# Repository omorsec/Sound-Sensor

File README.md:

# Sound-Sensor
It is a device that can be used to take input from the microphone and analyze it through different microcontrollers

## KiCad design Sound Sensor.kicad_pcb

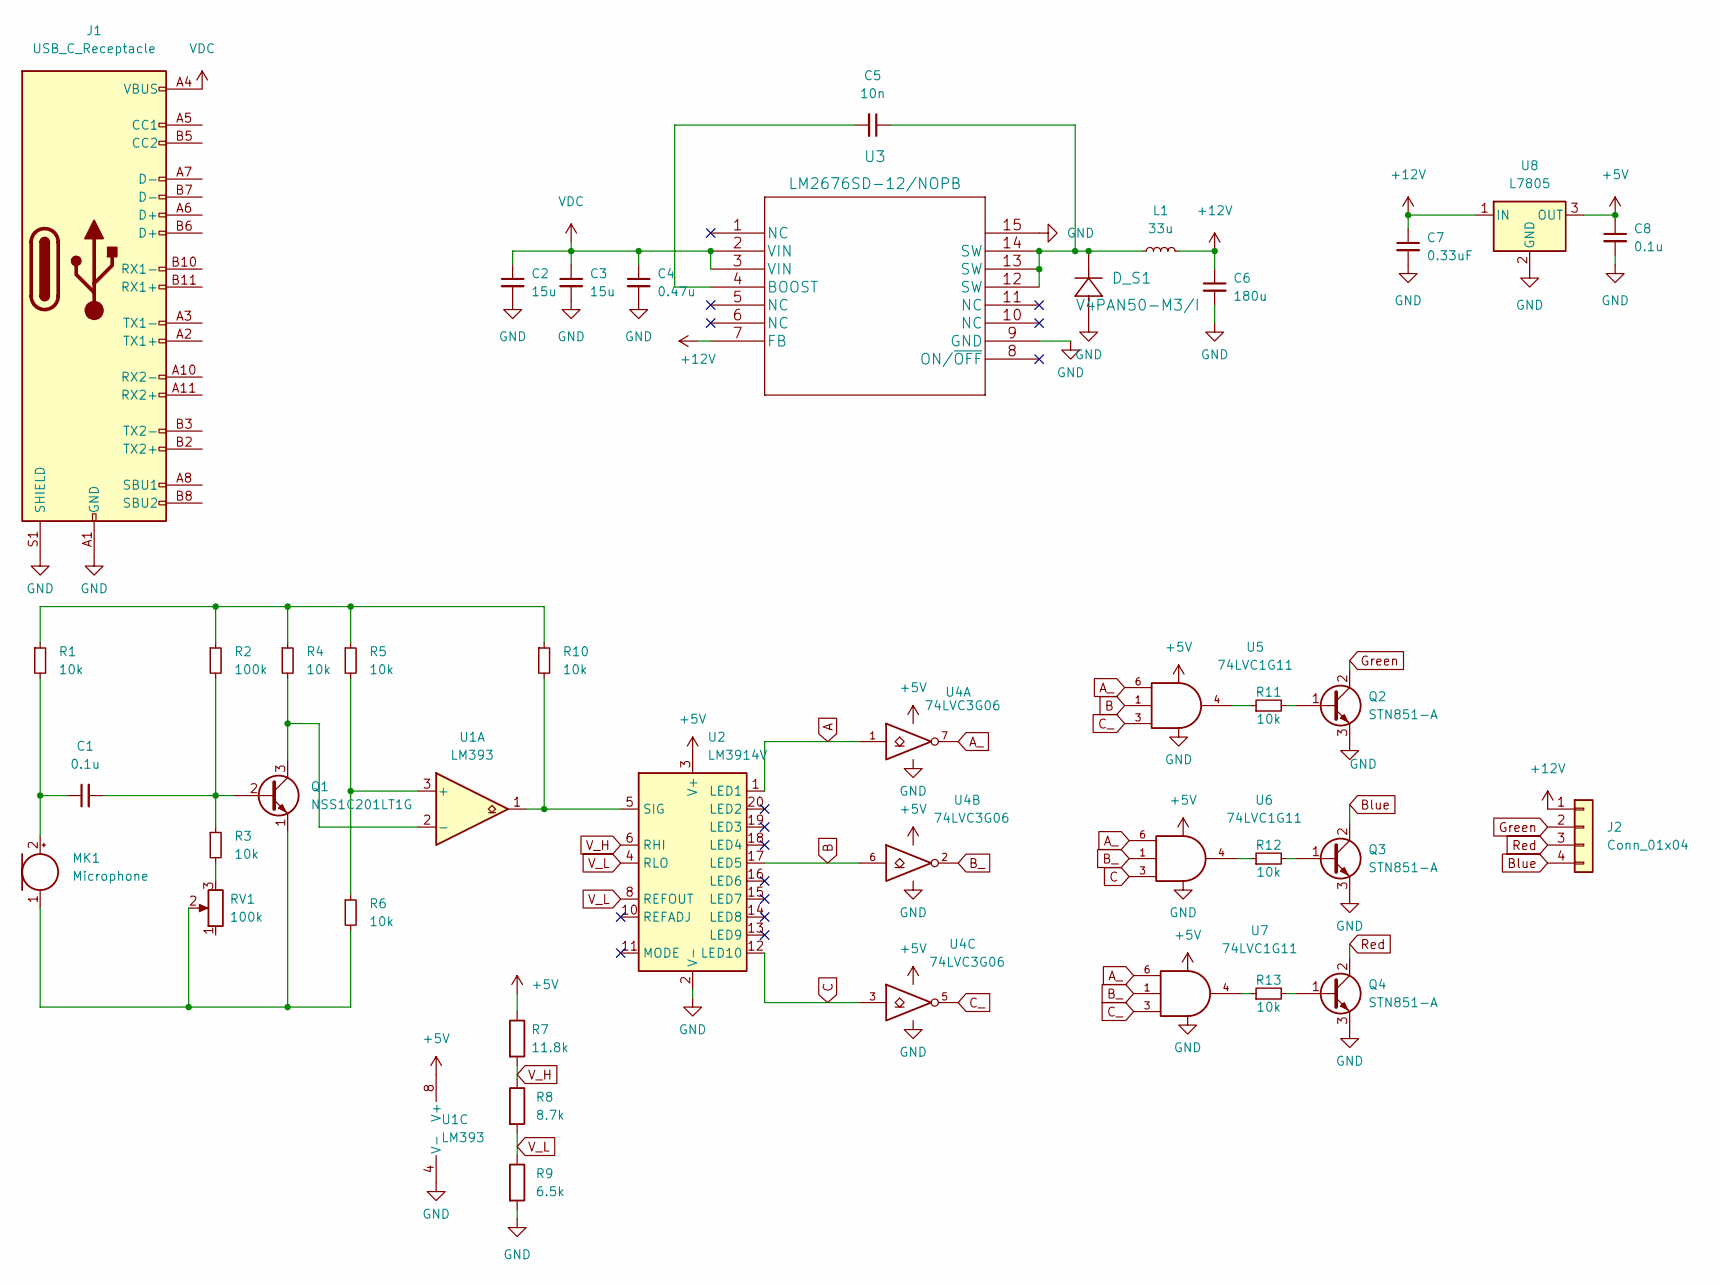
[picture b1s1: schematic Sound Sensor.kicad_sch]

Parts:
C1, C8: 0.1u; C_0402_1005Metric; Manufacturer Part No. CGA2B2X5R1A104K050BA
C2, C3: 15u; C_2220_5650Metric; Manufacturer Part No. C2220C156K5RAC7800
C4: 0.47u; C_0402_1005Metric; Manufacturer Part No. C1005X5R1E474K050BE
C5: 10n; C_0402_1005Metric; Manufacturer Part No. CGA2B3X7R1H103K050BB
C6: 180u; UPM1C181MED1TD; Manufacturer Part No. UPM1C181MED1TD
C7: 0.33uF; C_0805_2012Metric; Manufacturer Part No. C2012X8R1E334K125AA
D_S1: V4PAN50-M3/I; V4PAN50-M3&slash_I; Manufacturer Part No. V4PAN50-M3/I
J1: USB_C_Receptacle; USB_C_Receptacle_Amphenol_12401610E4-2A; Manufacturer Part No. 12401610E4#2A
J2: Conn_01x04; PinHeader_1x04_P2.54mm_Vertical; Manufacturer Part No. M20-9750446
L1: 33u; L_0805_2012Metric; Manufacturer Part No. LQM21DN330M70L
MK1: Microphone; MIC_AOM-4546P-R; Manufacturer Part No. AOM-4546P-R
Q1: NSS1C201LT1G; TO-236; Manufacturer Part No. NSS1C201LT1G
Q2, Q3, Q4: STN851-A; SOT-223; Manufacturer Part No. STN851-A
R1, R3, R4, R5, R6, R10, R11, R12, R13: 10k; R_0603_1608Metric; Manufacturer Part No. RNCP0603FTD10K0
R2: 100k; R_0603_1608Metric; Manufacturer Part No. RMCF0603JT100K
R7: 11.8k; R_0603_1608Metric; Manufacturer Part No. RMCF0603FT11K8
R8: 8.7k; R_0603_1608Metric; Manufacturer Part No. RMCF0603FT8K66
R9: 6.5k; R_0603_1608Metric; Manufacturer Part No. RNCP0603FTD6K49
RV1: 100k; SIP-3; Manufacturer Part No. CT94EY104
U1: LM393; SOIC-8 4mmx7mm; Manufacturer Part No. LM393EDR2G
U2: LM3914V; PLCC-20; Manufacturer Part No. LM3914V/NOPB
U3: LM2676SD-12/NOPB; LM2676SD-12&slash_NOPB; Manufacturer Part No. LM2676SD-12/NOPB
U4: 74LVC3G06; SN74LVC1G11DSFR; Manufacturer Part No. SN74LVC1G11DSFR
U5, U6, U7: 74LVC1G11; SOP50P310X90-8N; Manufacturer Part No. SN74LVC3G06DCUR
U8: L7805; DPak; Manufacturer Part No. L7805CDT-TR

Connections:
+5V: C8.1, R7.1, U1.8 (V+), U2.3 (V+), U4.8 (VCC), U5.5 (VCC), U6.5 (VCC), U7.5 (VCC), U8.3 (OUT)
+12V: C6.1, C7.1, J2.1, L1.2, U3.7 (FB), U8.1 (IN)
A: U2.1 (LED1), U4.1
A_: U4.7, U5.6, U6.6, U7.6
B: U2.17 (LED5), U4.6, U5.1
B_: U4.2, U6.1, U7.1
Blue: J2.4, Q3.2 (C), Q3.4
C: U2.12 (LED10), U4.3, U6.3
C_: U4.5, U5.3, U7.3
GND: C2.2, C3.2, C4.2, C6.2, C7.2, C8.2, D_S1.2, J1.A1 (GND), J1.A12 (GND), J1.B1 (GND), J1.B12 (GND), J1.S1 (SHIELD), Q2.3 (E), Q3.3 (E), Q4.3 (E), R9.2, U1.4 (V-), U2.2 (V-), U3.9 (GND), U3.15, U4.4 (GND), U5.2 (GND), U6.2 (GND), U7.2 (GND), U8.2 (GND)
Green: J2.2, Q2.2 (C), Q2.4
unnamed: C1.1, MK1.2 (+), R1.2
unnamed: C1.2, Q1.2 (B), R2.2, R3.1
unnamed: C5.1, D_S1.1, L1.1, U3.12 (SW), U3.13 (SW), U3.14 (SW)
unnamed: C5.2, U3.4 (BOOST)
unnamed: MK1.1 (-), Q1.1 (E), R6.2, RV1.2
unnamed: Q1.3 (C), R4.2, U1.2 (-)
unnamed: Q2.1 (B), R11.2
unnamed: Q3.1 (B), R12.2
unnamed: Q4.1 (B), R13.2
unnamed: R1.1, R2.1, R4.1, R5.1, R10.1
unnamed: R3.2, RV1.3
unnamed: R5.2, R6.1, U1.3 (+)
unnamed: R10.2, U1.1, U2.5 (SIG)
unnamed: R11.1, U5.4
unnamed: R12.1, U6.4
unnamed: R13.1, U7.4
Red: J2.3, Q4.2 (C), Q4.4
VDC: C2.1, C3.1, C4.1, J1.A4 (VBUS), J1.A9 (VBUS), J1.B4 (VBUS), J1.B9 (VBUS), U3.2 (VIN), U3.3 (VIN)
V_H: R7.2, R8.1, U2.6 (RHI)
V_L: R8.2, R9.1, U2.4 (RLO), U2.8 (REFOUT)

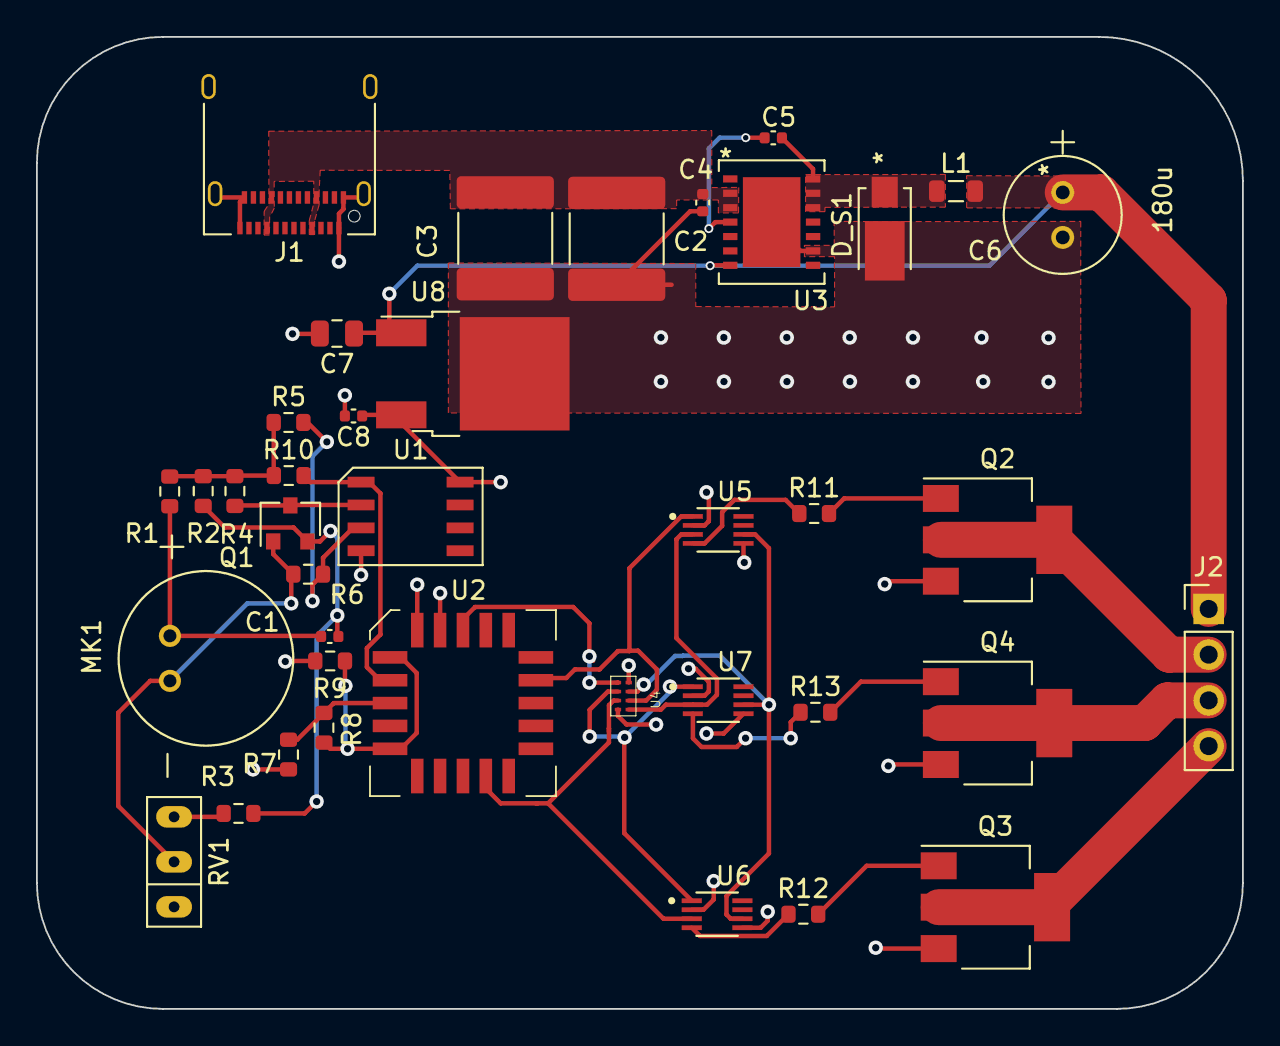
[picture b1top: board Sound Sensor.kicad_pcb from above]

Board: 4 copper layers, 67.0 x 54.0 mm, 39 parts (0 on the bottom side), 31 nets.

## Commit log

2023-01-13 Sound Sensor project final files
2023-01-13 Sound Sensor 3D view

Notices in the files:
parts and their libraries:
Copyright 2021 Accelerated Designs. All rights reserved.
